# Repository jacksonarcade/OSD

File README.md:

# OSD has video interface, esp8266 and microsd

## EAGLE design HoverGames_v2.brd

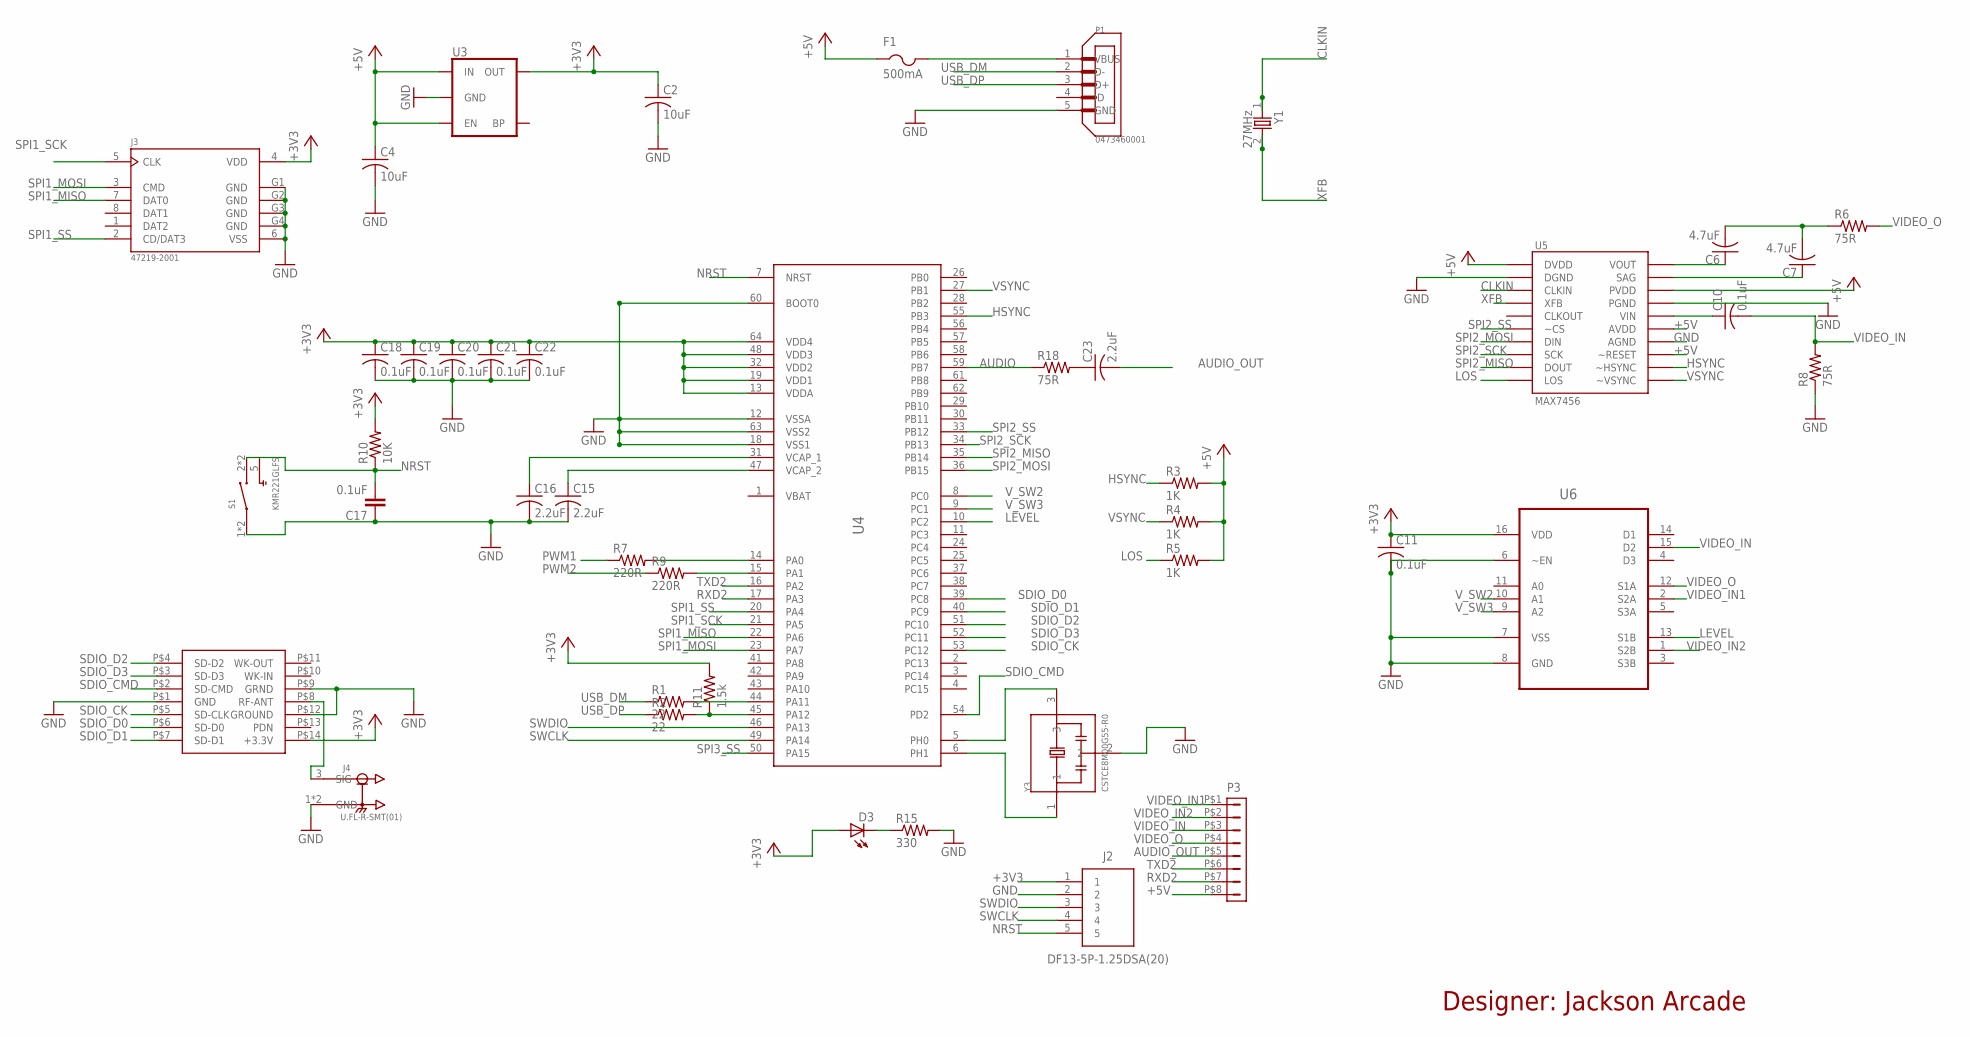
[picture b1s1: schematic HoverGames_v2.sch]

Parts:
C2, C4: 10uF; C0402
C6, C7: 4.7uF; C0402
C10, C11, C17, C18, C19, C20, C21, C22: 0.1uF; C0402
C15, C16, C23: 2.2uF; C0603
D3: LEDCHIP-LED0603; CHIP-LED0603
F1: 500mA; R1206
J2: DF13-5P-1.25DSA(20); SHDR5W43P0X125_1X5_790X340X460
J3: 47219-2001; MOLEX_47219-2001
J4: U.FL-R-SMT(01); HRS_U.FL-R-SMT(01)
P1: 0473460001; MOLEX_0473460001
P3: DF13-8P-1.25DSA
R1, R2: 22; R0402
R3, R4, R5: 1K; R0402
R6, R8, R18: 75R; R0402
R7, R9: 220R; R0402
R10: 10K; R0402
R11: 1.5k; R0402
R15: 330; R0402
S1: KMR221GLFS; SW_KMR221GLFS
U3: V_REG_SPX3819-SOT23-5; SOT23-5
U4: STM32F405XXSTM32F405XX; LQFP64
U5: MAX7456; TSSOP28
U6: ADG733BRUZ; SOP65P640X120-16N
U7: 88W8801
Y1: 27MHz; XTAL500X320X130N
Y3: CSTCE8M00G55-R0; OSC_CSTCE8M00G55-R0

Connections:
+3V3: C2.1, C11.1, C18.1, C19.1, C20.1, C21.1, C22.1, D3.A, J2.1, J3.4 (VDD), R10.2, R11.2, U3.5 (OUT), U4.13 (VDDA), U4.19 (VDD1), U4.32 (VDD2), U4.48 (VDD3), U4.64 (VDD4), U6.16 (VDD), U7.P$14 (+3.3V)
+5V: C4.1, F1.1, P3.P$8 (8), R3.2, R4.2, R5.2, U3.1 (IN), U3.3 (EN), U5.3 (DVDD), U5.19 (~RESET), U5.21 (AVDD), U5.24 (PVDD)
AUDIO: R18.1, U4.59 (PB7)
AUDIO_OUT: C23.2, P3.P$5 (5)
CLKIN: U5.5 (CLKIN), Y1.1
GND: C2.2, C4.2, C11.2, C15.2, C16.2, C17.1, C18.2, C19.2, C20.2, C21.2, C22.2, J2.2, J3.6 (VSS), J3.G1 (GND), J3.G2 (GND), J3.G3 (GND), J3.G4 (GND), J4.1 (GND), J4.2 (GND), P1.5 (GND), R8.1, R15.2, S1.1, S1.4 (1), U3.2 (GND), U4.12 (VSSA), U4.18 (VSS1), U4.60 (BOOT0), U4.63 (VSS2), U5.4 (DGND), U5.20 (AGND), U5.23 (PGND), U6.6 (~EN), U6.7 (VSS), U6.8 (GND), U7.P$1 (GND), U7.P$9 (GRND), U7.P$12 (GROUND), Y3.2
HSYNC: R3.1, U4.55 (PB3), U5.18 (~HSYNC)
LEVEL: U4.10 (PC2), U6.13 (S1B)
LOS: R5.1, U5.12 (LOS)
unnamed: R7.2, U4.14 (PA0)
unnamed: R9.2, U4.15 (PA1)
unnamed: C23.1, R18.2
unnamed: J4.3 (SIG), U7.P$8 (RF-ANT)
unnamed: C16.1, U4.31 (VCAP_1)
unnamed: R1.2, U4.44 (PA11)
unnamed: C15.1, U4.47 (VCAP_2)
unnamed: R2.2, R11.1, U4.45 (PA12)
unnamed: C6.1, U5.26 (VOUT)
unnamed: C7.1, U5.25 (SAG)
unnamed: C6.2, C7.2, R6.1
unnamed: C10.1, U5.22 (VIN)
unnamed: F1.2, P1.1 (VBUS)
unnamed: U4.6 (PH1), Y3.1
unnamed: D3.C, R15.1
unnamed: U4.5 (PH0), Y3.3
NRST: C17.2, J2.5, R10.1, S1.2 (3), S1.3, U4.7 (NRST)
PWM1: R7.1
PWM2: R9.1
RXD2: P3.P$7 (7), U4.17 (PA3)
SDIO_CK: U4.53 (PC12), U7.P$5 (SD-CLK)
SDIO_CMD: U4.54 (PD2), U7.P$2 (SD-CMD)
SDIO_D0: U4.39 (PC8), U7.P$6 (SD-D0)
SDIO_D1: U4.40 (PC9), U7.P$7 (SD-D1)
SDIO_D2: U4.51 (PC10), U7.P$4 (SD-D2)
SDIO_D3: U4.52 (PC11), U7.P$3 (SD-D3)
SPI1_MISO: J3.7 (DAT0), U4.22 (PA6)
SPI1_MOSI: J3.3 (CMD), U4.23 (PA7)
SPI1_SCK: J3.5 (CLK), U4.21 (PA5)
SPI1_SS: J3.2 (CD/DAT3), U4.20 (PA4)
SPI2_MISO: U4.35 (PB14), U5.11 (DOUT)
SPI2_MOSI: U4.36 (PB15), U5.9 (DIN)
SPI2_SCK: U4.34 (PB13), U5.10 (SCK)
SPI2_SS: U4.33 (PB12), U5.8 (~CS)
SPI3_SS: U4.50 (PA15)
SWCLK: J2.4, U4.49 (PA14)
SWDIO: J2.3, U4.46 (PA13)
TXD2: P3.P$6 (6), U4.16 (PA2)
USB_DM: P1.2 (D-), R1.1
USB_DP: P1.3 (D+), R2.1
VBAT: U4.1 (VBAT)
VIDEO_IN: C10.2, P3.P$3 (3), R8.2, U6.15 (D2)
VIDEO_IN1: P3.P$1 (1), U6.2 (S2A)
VIDEO_IN2: P3.P$2 (2), U6.1 (S2B)
VIDEO_O: P3.P$4 (4), R6.2, U6.12 (S1A)
VSYNC: R4.1, U4.27 (PB1), U5.17 (~VSYNC)
V_SW2: U4.8 (PC0), U6.10 (A1)
V_SW3: U4.9 (PC1), U6.9 (A2)
XFB: U5.6 (XFB), Y1.2

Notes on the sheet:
Designer: Jackson Arcade

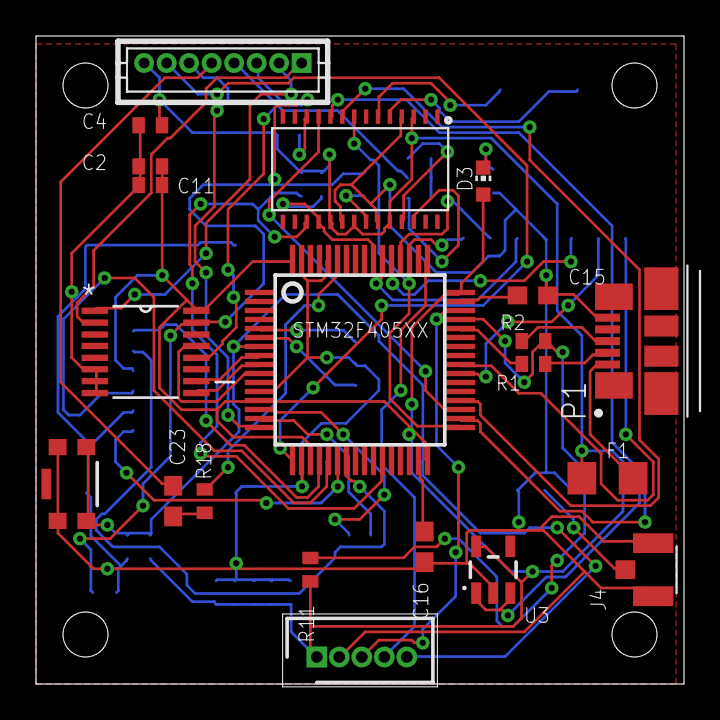
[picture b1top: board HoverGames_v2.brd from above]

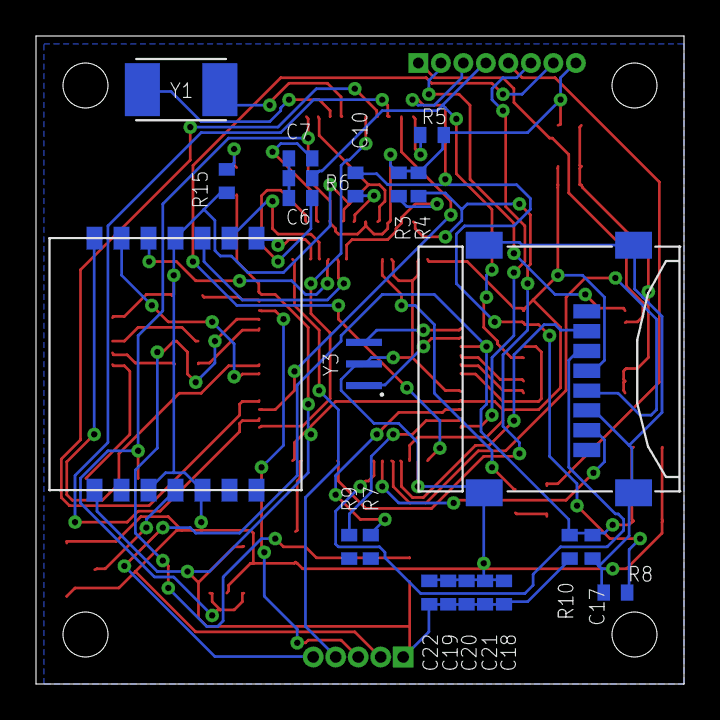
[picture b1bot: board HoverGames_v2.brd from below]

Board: 2 copper layers, 36.0 x 36.0 mm, 43 parts (22 on the bottom side), 54 nets.

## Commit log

2018-02-08 Add files

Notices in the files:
parts and their libraries:
SparkFun-Retired: Licensing: Creative Commons ShareAlike 4.0 International - https://creativecommons.org/licenses/by-sa/4.0
